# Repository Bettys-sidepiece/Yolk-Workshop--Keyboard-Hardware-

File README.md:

## License

The Yolk Keyboard hardware is licensed under the **TAPR Open Hardware License (TAPR OHL).**  
  
[Read the full license](https://www.tapr.org/ohl.html)  

### **About the Yolk Keyboard Hardware**
The Yolk Keyboard consists of four PCBs:
- **Slaptic System**: Slide + haptic feedback module
- **Germinal Disc**: Keyboard (human input device)
- **Vitillus**: Main controller PCB
- **Proximity Sensor**: Detects user presence

### **Core Components**
- **Microcontroller**: STM32L702
- **Bluetooth Module**: Microchip BM71 for BLE connectivity
- **Lighting**: RGB LEDs
- **Additional Features**: Haptic feedback, capacitive touch sensing, and advanced power management

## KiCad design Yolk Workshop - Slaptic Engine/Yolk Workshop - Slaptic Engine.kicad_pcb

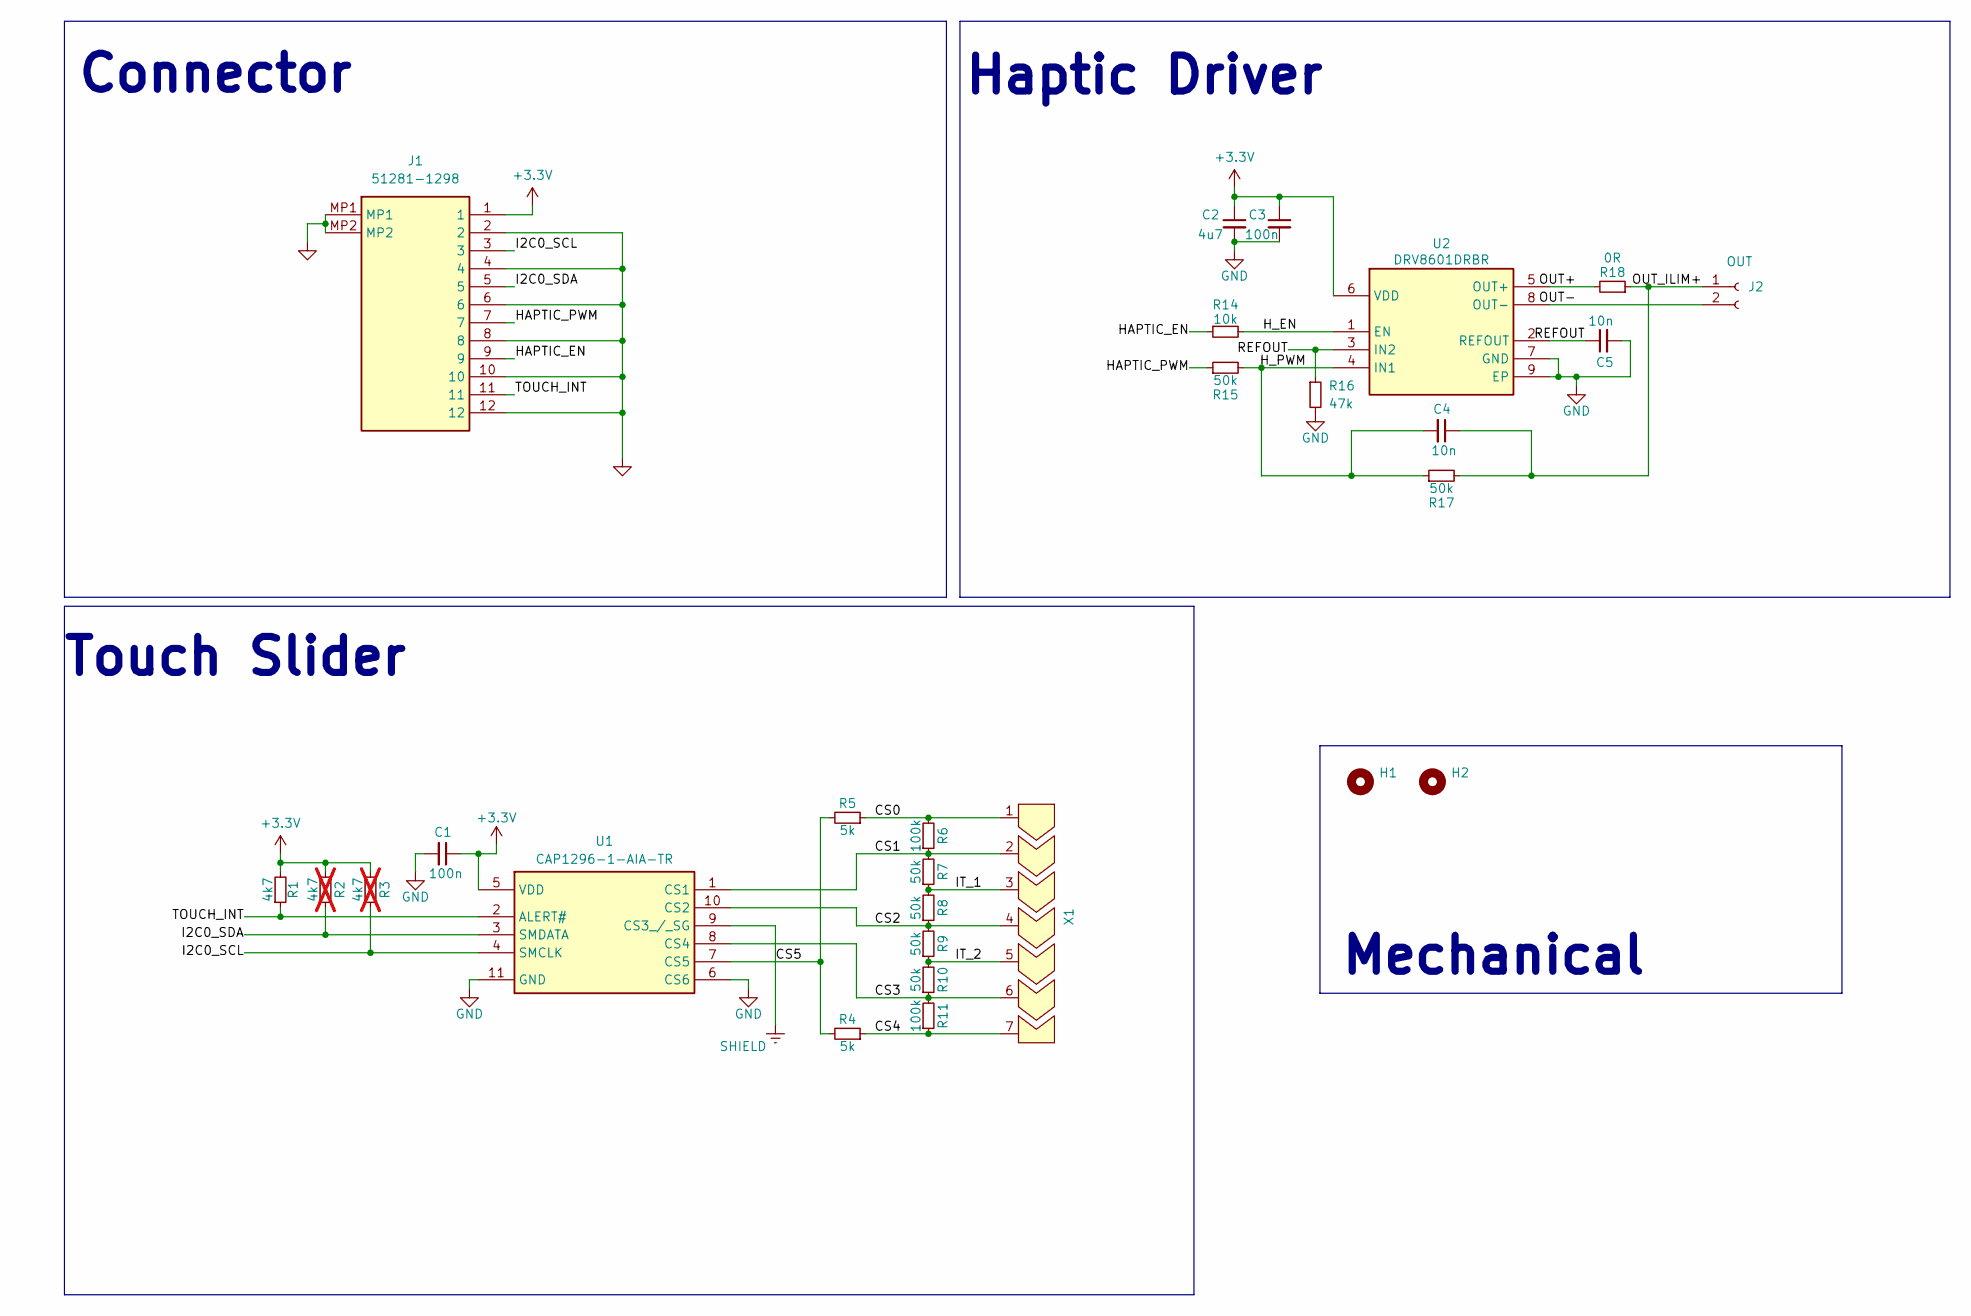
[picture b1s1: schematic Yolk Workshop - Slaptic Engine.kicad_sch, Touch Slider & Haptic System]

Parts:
C1, C3: 100n; C_0402_1005Metric
C2: 4u7; C_0402_1005Metric
C4, C5: 10n; C_0402_1005Metric
H1, H2: MountingHole; MountingHole_2.1mm
J1: 51281-1298; 512811298; Manufacturer_Part_Number 51281-1298; Mouser Part Number 538-51281-1298
J2: OUT; PinHeader_1x02_P2.00mm_Vertical
R1: 4k7; R_0402_1005Metric
R2, R3: 4k7; R_0402_1005Metric; not fitted
R4, R5: 5k; R_0402_1005Metric
R6, R11: 100k; R_0402_1005Metric
R7, R8, R9, R10, R15, R17: 50k; R_0402_1005Metric
R14: 10k; R_0402_1005Metric
R16: 47k; R_0402_1005Metric
R18: 0R; R_0402_1005Metric
U1: CAP1296-1-AIA-TR; SON50P300X300X90-11N-D; Manufacturer_Part_Number CAP1296-1-AIA-TR; Mouser Part Number 579-CAP1296-1-AIA-TR
U2: DRV8601DRBR; SON65P300X300X100-9N-D; Manufacturer_Part_Number DRV8601DRBR; Mouser Part Number 595-DRV8601DRBR
X1: Capacitive_slider_8x70

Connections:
+3.3V: C1.1, C2.1, C3.1, J1.1, R1.2, R2.2, R3.2, U1.5 (VDD), U2.6 (VDD)
/CS0: R5.1, R6.2, X1.1
/CS1: R6.1, R7.2, U1.1 (CS1), X1.2
/CS2: R8.1, R9.2, U1.10 (CS2), X1.4
/CS3: R10.1, R11.2, U1.8 (CS4), X1.6
/CS4: R4.1, R11.1, X1.7
/CS5: R4.2, R5.2, U1.7 (CS5)
/HAPTIC_EN: J1.9, R14.1
/HAPTIC_PWM: J1.7, R15.1
/H_EN: R14.2, U2.1 (EN)
/H_PWM: C4.2, R15.2, R17.1, U2.4 (IN1)
/I2C0_SCL: J1.3, R3.1, U1.4 (SMCLK)
/I2C0_SDA: J1.5, R2.1, U1.3 (SMDATA)
/IT_1: R7.1, R8.2, X1.3
/IT_2: R9.1, R10.2, X1.5
/OUT+: R18.2, U2.5 (OUT+)
/OUT-: J2.2, U2.8 (OUT-)
/OUT_ILIM+: C4.1, J2.1, R17.2, R18.1
/REFOUT: C5.1, R16.1, U2.2 (REFOUT), U2.3 (IN2)
/TOUCH_INT: J1.11, R1.1, U1.2 (ALERT#)
GND: C1.2, C2.2, C3.2, C5.2, J1.2, J1.4, J1.6, J1.8, J1.10, J1.12, J1.MP1, J1.MP2, R16.2, U1.6 (CS6), U1.11 (GND), U2.7 (GND), U2.9 (EP)
SHIELD: U1.9 (CS3_/_SG)

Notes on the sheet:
Connector
Mechanical
Haptic Driver
Touch Slider

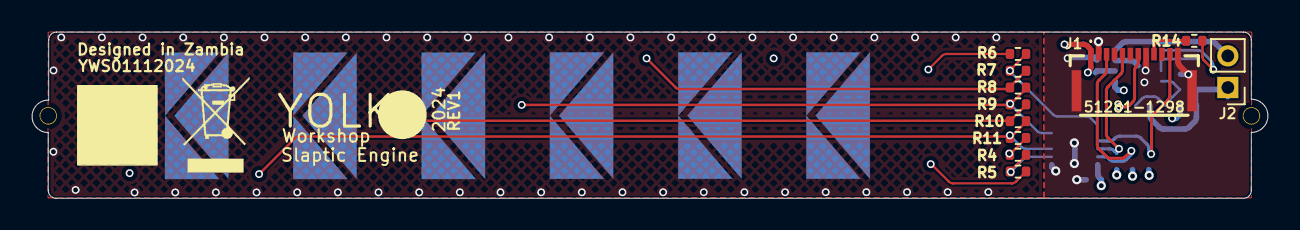
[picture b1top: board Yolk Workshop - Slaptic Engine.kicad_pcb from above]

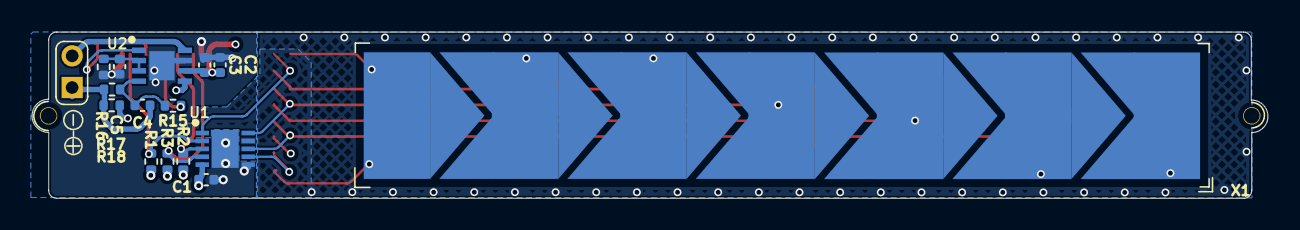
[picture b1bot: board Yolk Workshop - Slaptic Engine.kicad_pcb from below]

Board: 4 copper layers, 78.1 x 10.5 mm, 28 parts (15 on the bottom side), 21 nets.

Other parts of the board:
H2#2: MountingHole; MountingHole_2.1mm

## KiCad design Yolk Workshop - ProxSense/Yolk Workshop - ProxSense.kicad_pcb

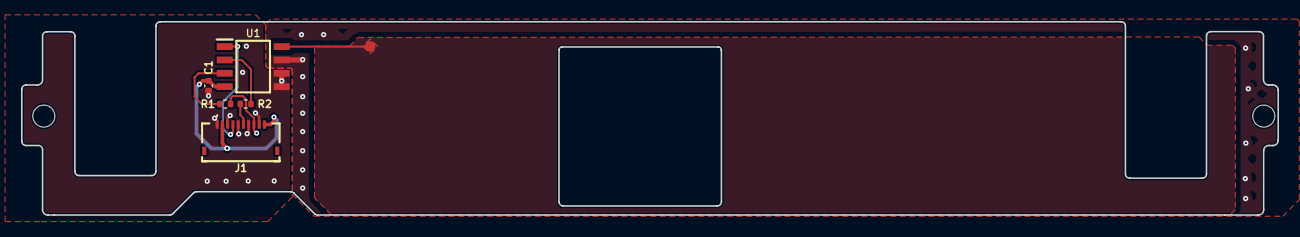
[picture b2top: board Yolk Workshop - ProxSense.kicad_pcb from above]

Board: 2 copper layers, 119.6 x 18.4 mm, 5 parts (0 on the bottom side), 7 nets.

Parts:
C1: 100n; C_0402_1005Metric
J1: 046809610110846
R1, R2: 0R; R_0402_1005Metric
U1: CAP1293-1-SN; SOIC127P600X175-8N

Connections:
+3.3V: C1.1, J1.2, J1.10, U1.4 (VDD)
/EXT_ALRT: J1.4, U1.1 (ALERT#)
/EXT_SCL: J1.8, R1.2
/EXT_SDA: J1.6, R2.2
/I2C_SCL: R1.1, U1.3 (SMCLK)
/I2C_SDA: R2.1, U1.2 (SMDAT)
GND: C1.2, J1.1, J1.3, J1.5, J1.7, J1.9, U1.5 (GND), U1.6 (CS3)

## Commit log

2024-12-10 git init
2024-12-11 added license file
2025-02-09 updates to HIP and Controller design
2025-02-09 License Updated
2025-02-09 CC-BY-SA License Added
